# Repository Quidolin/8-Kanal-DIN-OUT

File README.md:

# 8-Kanal-DIN-OUT
Switch and LED addon board for 8-Kanal-DIN-BASE output for HomeMatic HM-MOD-Re-8
Eagle-Project

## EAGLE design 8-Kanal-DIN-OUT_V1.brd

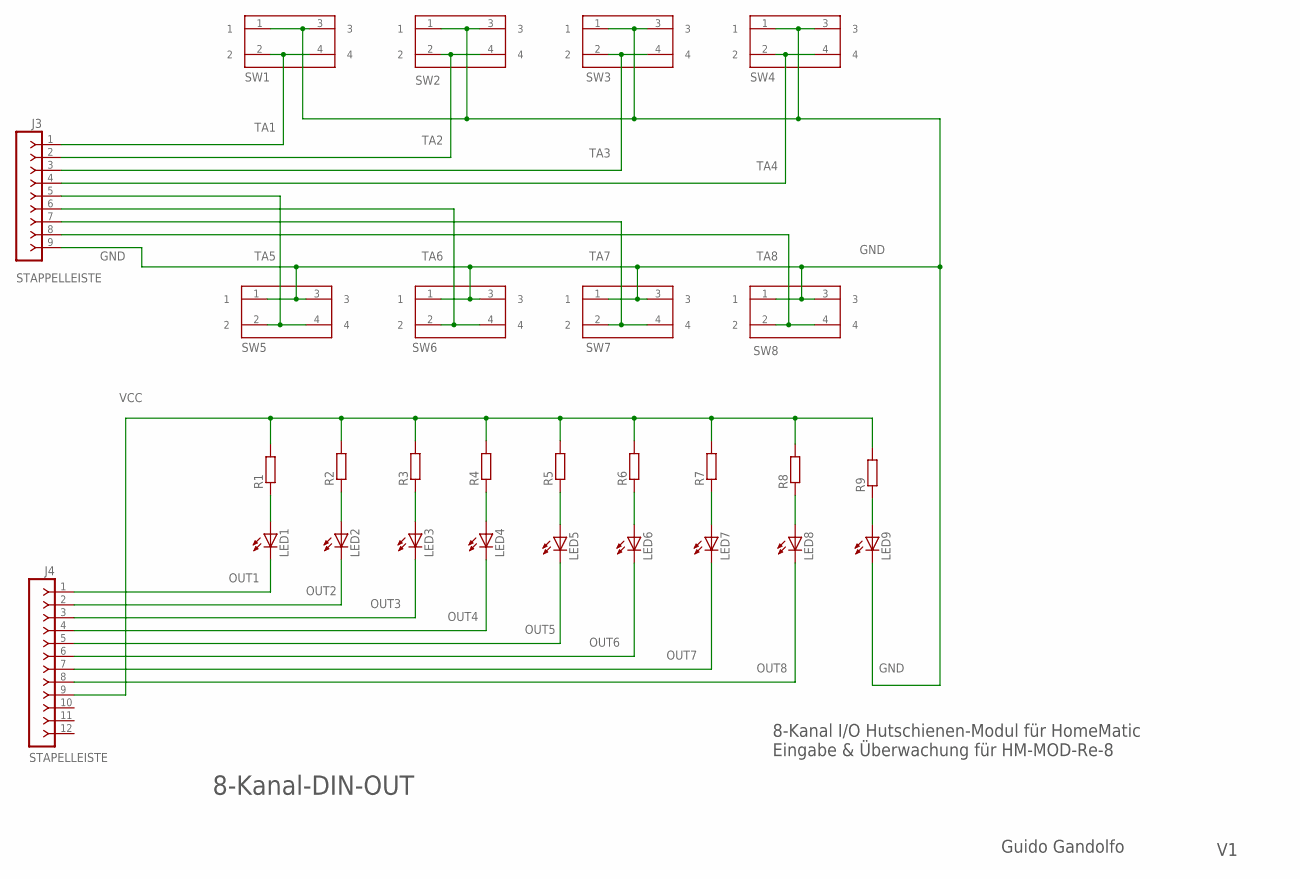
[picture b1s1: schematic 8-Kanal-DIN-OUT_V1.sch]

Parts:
J3: STAPPELLEISTE; SIP-100-09-40Y
J4: STAPELLEISTE; SIP-100-12-40Y
LED1, LED2, LED3, LED4, LED5, LED6, LED7, LED8, LED9: LED3MM
R1, R2, R3, R4, R5, R6, R7, R8, R9: R-EU_0207/2V; 0207/2V
SW1, SW2, SW3, SW4, SW5, SW6, SW7, SW8: TASTER 9305; 430156130936

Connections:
GND: J3.9, LED9.K (C), SW1.1, SW1.3, SW2.1, SW2.3, SW3.1, SW3.3, SW4.1, SW4.3, SW5.1, SW5.3, SW6.1, SW6.3, SW7.1, SW7.3, SW8.1, SW8.3
unnamed: LED1.A, R1.1
unnamed: LED2.A, R2.1
unnamed: LED3.A, R3.1
unnamed: LED4.A, R4.1
unnamed: LED5.A, R5.1
unnamed: LED6.A, R6.1
unnamed: LED7.A, R7.1
unnamed: LED8.A, R8.1
unnamed: LED9.A, R9.1
OUT1: J4.1, LED1.K (C)
OUT2: J4.2, LED2.K (C)
OUT3: J4.3, LED3.K (C)
OUT4: J4.4, LED4.K (C)
OUT5: J4.5, LED5.K (C)
OUT6: J4.6, LED6.K (C)
OUT7: J4.7, LED7.K (C)
OUT8: J4.8, LED8.K (C)
TA1: J3.1, SW1.2, SW1.4
TA2: J3.2, SW2.2, SW2.4
TA3: J3.3, SW3.2, SW3.4
TA4: J3.4, SW4.2, SW4.4
TA5: J3.5, SW5.2, SW5.4
TA6: J3.6, SW6.2, SW6.4
TA7: J3.7, SW7.2, SW7.4
TA8: J3.8, SW8.2, SW8.4
VCC: J4.9, R1.2, R2.2, R3.2, R4.2, R5.2, R6.2, R7.2, R8.2, R9.2

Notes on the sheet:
8-Kanal-DIN-OUT
8-Kanal I/O Hutschienen-Modul für HomeMatic Eingabe & Überwachung für HM-MOD-Re-8
Guido Gandolfo

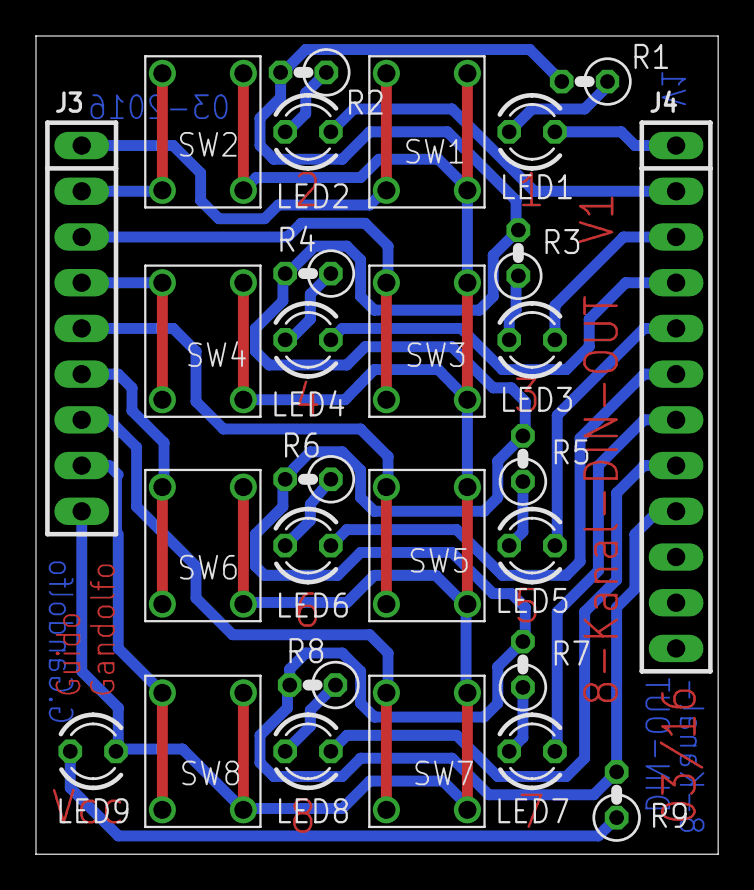
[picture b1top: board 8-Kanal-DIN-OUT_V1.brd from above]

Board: 2 copper layers, 37.9 x 45.5 mm, 28 parts (0 on the bottom side), 27 nets.

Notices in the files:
parts and their libraries:
con-headers-jp: Copyright (C) 2008, Bob Starr
Switch_rev16b_wurth: Copyright: Würth Elektronik
